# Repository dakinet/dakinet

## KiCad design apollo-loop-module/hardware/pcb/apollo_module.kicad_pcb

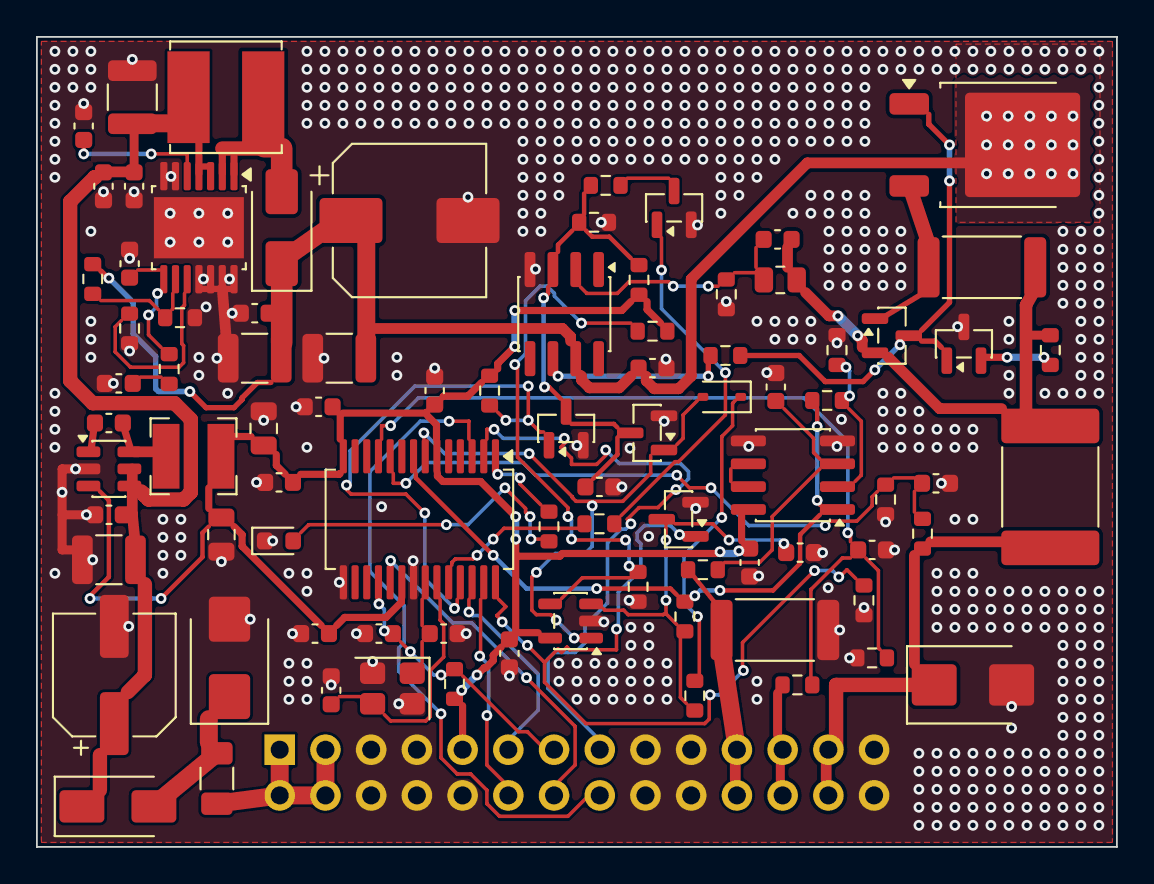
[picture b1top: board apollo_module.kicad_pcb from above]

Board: 2 copper layers, 60.0 x 45.0 mm, 86 parts (1 on the bottom side), 49 nets.

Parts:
C1: 47u/50V; CP_Elec_6.3x7.7
C2, C3, C4, C11: 10u/50V; C_1210_3225Metric
C5: 100u/50V; CP_Elec_8x10
C6, C10, C20, C23, C25, C28, C29: 100n; C_0603_1608Metric
C7, C16: 100p; C_0603_1608Metric
C8: 47n; C_0603_1608Metric
C9: 1u/50V; C_0603_1608Metric
C12: 22u/10V; C_0805_2012Metric
C13: 10u; C_0805_2012Metric
C14, C30: 10n; C_0603_1608Metric
C15, C35, C36, C37: 100n/50V; C_0603_1608Metric
C17, C18, C19, C24: 1n; C_0603_1608Metric
C26, C27: 27p; C_0603_1608Metric
C32: 1u; C_0603_1608Metric
D1: SS34; D_SMA
D2: SS210; D_SMA
D3: SMBJ36A; D_SMB
D4: BAT54J; D_SOD-323
D5: LED; LED_0603_1608Metric
D6: SMBJ28A; D_SMB
F1: 3A; Fuse_1206_3216Metric
F2: PTC 750mA/60V; Fuse_2920_7451Metric
J1: MATICNA 2x14; PinHeader_2x14_P2.54mm_Vertical
L1: 33uH SRN6045TA-330M; L_Bourns_SRN6045TA
L2: 15uH SRN4018-150M; L_Bourns-SRN4018
Q1: MJD122; TO-252-2
Q2, Q3, Q6, Q7: 2N7002; SOT-23
Q4: MMBT3904; SOT-23
Q5: MMBT5401; SOT-23
R1: 270k; R_0603_1608Metric
R2, R12, R16, R18, R21, R25, R26, R29: 10k; R_0603_1608Metric
R3: 82k; R_0603_1608Metric
R4: 2k2; R_0603_1608Metric
R5, R20, R27, R35: 1k; R_0603_1608Metric
R6: 15k; R_0603_1608Metric
R7: 3k24; R_0603_1608Metric
R8: 100; R_0603_1608Metric
R9, R15, R17, R28: 100k; R_0603_1608Metric
R10: 470; R_0603_1608Metric
R11: 91k; R_0805_2012Metric
R13: 2R0 1W; R_2512_6332Metric
R14: 10; R_0603_1608Metric
R19: 1R 1W; R_2512_6332Metric
R22: 40k2; R_0603_1608Metric
R24: 13k; R_0603_1608Metric
U1: TPS55340PWPR; Texas_HTSSOP-14-1EP_4.4x5mm_P0.65mm_EP3.4x5mm_Mask3.155x3.2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
U2: TPS560430X3FDBVR; SOT-23-6
U3: OPA197; SOIC-8_3.9x4.9mm_P1.27mm
U4: MCP6002; SOIC-8_3.9x4.9mm_P1.27mm
U6: MCP6561T-E/OT; SOT-23-5
U7: AVR64DD28-I/SS; SSOP-28_5.3x10.2mm_P0.65mm
Y1: 16MHz X322516MLB4SI; Crystal_SMD_3225-4Pin_3.2x2.5mm

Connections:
+3V3: C12.1, C13.1, C20.1, C23.1, C25.1, C28.1, C29.1, C32.1, J1.9, L2.2, R5.1, R9.2, R24.1, R29.2, U2.3, U4.8, U6.5, U7.6, U7.14, U7.20
+24V_IN: F1.1, J1.1, J1.2, J1.3, J1.4
+34V: C3.1, C4.1, C5.1, C15.1, C36.1, D2.1, Q1.2, R1.1, U3.7
BFB: R1.2, R2.1, U1.9
CB: C10.1, U2.1
CC: C6.1, R4.2
COMP: C7.1, R4.1, U1.8
DBG_RX: J1.16, U7.3
DBG_TX: J1.15, U7.2
EN_N: Q3.1, R9.1, U7.25
FB: C16.2, R11.2, R12.1, U3.2
FREQ: R3.1, U1.10
GND: C1.2, C2.2, C3.2, C4.2, C5.2, C6.2, C7.2, C8.2, C9.2, C11.2, C12.2, C13.2, C14.2, C15.2, C17.2, C18.2, C19.2, C20.2, C23.2, C24.2, C25.2, C26.2, C27.2, C28.2, C29.2, C30.2, C32.2, C35.2, C36.2, C37.2, D3.2, D5.1, D6.2, J1.5, J1.6, J1.7, J1.8, J1.10, J1.17, J1.18, J1.19, J1.20, J1.27, J1.28, Q2.2, Q3.2, Q5.3, Q6.2, Q7.2, R2.2, R3.2, R6.2, R12.2, R16.2, R18.2, R19.2, R21.2, R25.2, R28.2, U1.6, U1.7, U1.11, U1.12, U1.13, U1.14, U1.15, U2.2, U3.4, U4.4, U4.5, U6.2, U7.15, U7.21, Y1.2, Y1.4
IAMP: R22.2, R26.1, U4.1, U7.8
ISENSE: J1.21, J1.22, R19.1, R20.1
LED: R35.1, U7.1
LED_A: D5.2, R35.2
LOOP_DRV: C16.1, F2.1, Q4.2, R11.1, R13.2, R14.2
LOOP_IN: J1.23, J1.24, R17.1
LOOP_OUT: D3.1, F2.2, J1.25, J1.26, R15.1
NA: C19.1, R20.2, U4.3
NB: Q1.1, Q4.3, Q5.1, R10.2
NE: Q1.3, Q4.1, R13.1
NIVO: R8.1, U7.24
NIVO_G: Q2.1, R8.2
NM: R21.1, R22.1, U4.2
OCP: D4.2, Q6.1, U6.1, U7.7
OC_FB: D4.1, R27.1
OC_IN: C24.1, Q7.3, R26.2, R27.2, U6.3
OC_REF: R24.2, R25.1, U6.4
OC_RST: Q7.1, R28.1, U7.28
PE: Q5.2, R14.1
Q2D: Q2.3, R7.2
RESET: C30.1, J1.13, R29.1, U7.18
RX: J1.12, U7.27
SS: C8.1, U1.5
SW: D2.2, L1.2, U1.1, U1.2
SW3: C10.2, L2.1, U2.6
TX: J1.11, U7.26
U3OUT: R10.1, U3.6
U4B: U4.6, U4.7
UPDI: J1.14, U7.19
VIN: C1.1, C2.1, C9.1, C11.1, C35.1, C37.1, D1.1, L1.1, U1.3, U1.4, U2.4, U2.5
VIN_F: D1.2, D6.1, F1.2
VLOOP: C17.1, R15.2, R16.1, U7.10
VRET: C18.1, R17.2, R18.1, U7.11
VSET: C14.1, Q3.3, Q6.3, R5.2, R6.1, R7.1, U3.3
XIN: C26.1, U7.22, Y1.1
XO: C27.1, U7.23, Y1.3

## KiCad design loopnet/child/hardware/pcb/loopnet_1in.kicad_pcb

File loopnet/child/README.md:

# LoopNet 1IN v0.1 – uređaj sa jednim ulazom

Uređaj na LoopNet petlji (`../PROTOCOL.md` v0.2): napaja se sa dvožične linije, čita jedan kontakt sa EOL otpornicima,
odgovara strujnim impulsom 10 mA. Pločica 30 × 20 mm, 2 sloja, sve SMD na gornjoj strani (osim stezaljki).
**Nije protivpožarni uređaj.**

```
hardware/schematic/   kompletna.svg/png: cela šema na jednom listu, svi elementi povezani; skripta kompletna.py (schemdraw)
hardware/3d/          index.html + loopnet_1in.wrl: interaktivni 3D prikaz (three.js); pravi ga pcb/export_3d.py
hardware/pcb/         make_pcb.py (raspored + mreže) -> Freerouting -> finish_pcb.py -> DRC (build.sh)
                      jlc.py: Gerber zip, BOM_JLC.csv, CPL_JLC.csv; render.py: pcb_pregled.png
firmware/             C za ATtiny1616 (avr-gcc): ln_proto.c (dekoder okvira), crt0.S, test/test_decode.py
```

## Blokovi

| Blok | Delovi | Funkcija |
|---|---|---|
| Linija | J1 ulaz, J2 izlaz (prolazno, LA/LB), D1+D2 2× BAV99 most, D3 SMAJ40A | polaritet nebitan; TVS iza mosta |
| Izvor struje | Q1 MMBT5551, Q2 MMBT3904, R1 1M, R2 3k3, D4 BZT52C10, C1 10 µF | **konstantna** struja sa linije I = Vbe(Q2)/R2 + VP/R1 ≈ 167 + 24 µA; višak kroz Zener 10 V |
| 3,3 V | U1 HT7533-1 (SOT-89, JLC Basic), C2 10 µF, C3 100 nF | Iq 2,5 µA, ulaz do 24–30 V (VC je 10 V iza Zenera) |
| Prijem | R3, R4 4M7 sa **obe žice pre mosta** → LINE (PA7), R5 330k | čvor prati liniju i na silaznoj ivici (iza mosta bi TVS kapacitet držao vrh) |
| Prag | C4 10 nF na PA6 (AC0−), puni ga DAC0 ~50 µs svakih 10 ms | osnovni nivo (ADC na PA7) + 3,5 V |
| Odgovor | Q3 MMBT5551, R6 270 Ω, R7 1k, R8 100k | (3,3 − 0,75) V / 270 Ω ≈ 9,4 mA iz VP, samo za vreme odgovora (≤ 100 µs, ~0,27 W u impulsu) |
| Ulaz | J3, R9 2k2 sa PA3 (uključen ~50 µs), R10 1k + C5 1 nF → PA4 (ADC) | EOL 2k2 serijski + 2k2 paralelno kontaktu |
| Buđenje | PA5 (AC0 OUT) vodom na PA2 | AC0 u STANDBY-u ne postavlja zastavicu ni prekid (samo OUT pin i događaj); PA2 ima potpuno asinhronu detekciju ivice i budi CPU |
| Ostalo | D5 crvena LED + R11 1k (PB1), SW1 taster (PB2, interni pull-up), J4 UPDI 1,27 mm (VDD, PA0, GND) | |

## Odstupanja od zadatih delova (i zašto)

| Zadato | Urađeno | Razlog |
|---|---|---|
| MB6S | 2× BAV99 (SOT-23, 100 V, LCSC C2500 basic) | KiCad 7 nema MBS/TO-269AA otisak, a Vishay/Diodes datasheet-ovi nisu dostupni iz kontejnera – raspored pinova i otisak MB6S nisam mogao da proverim. BAV99 ima standardan raspored (1 A, 2 K, 3 sredina), 1,5 pF umesto ~15 pF. Struja ≤ 10 mA, napon ≤ 64 V (TVS). |
| BSS126 (~0,5 mA limiter) | izvor struje sa 2 NPN, ~180 µA | Limiter od 0,5 mA bez Zenera puni kondenzator do vrha (31 V) samo za vreme impulsa: osnovna struja u prozorima bi skakala do 60 mA za 120 uređaja i prag mastera bi bio pogrešan (PROTOCOL §0). Uz Zener uređaj vuče stalno I_CC; BSS126 ima V_GS(off) rasipanje ~2:1, pa bi I_CC bio 2:1 – Vbe/R izvor drži ±10 % (0–50 °C). |
| Referenca = „filtrirani osnovni nivo + 3 V“ (RC) | ADC meri osnovni nivo, DAC0 puni C4 (sample-hold) na +3,5 V | RC usrednjavanje zavisi od gustine impulsa; proračun u PROTOCOL §1.2 pokazuje da fiksni odnos ne radi za 15–26 V. VREF + DAC stalno uključeni ne bi stali u budžet. |

### Zamena Extended → Basic (JLC)

| Ranije (Extended) | Sada | Napomena |
|---|---|---|
| TPS7B8133DRV (WSON-6) | HT7533-1 SOT-89, C14289 | VC je ograničen Zenerom na 10 V, pa 40 V ulaz nije potreban; raspored pinova proveriti |
| BCX56-16 (SOT-89) | MMBT5551 SOT-23, C2145 | 160 V, 600 mA; ~0,27 W samo u impulsima odgovora |
| R6 240 Ω 0402 | 270 Ω 0603, C22966 | odgovor ~9,4 mA (spec 10 mA ±20 %) |
| R1 2M2 | 1M 0603, C22935 | +13 µA u izvoru struje |
| R5 330k 0402 | 330k 0603, C23137 | |
| R2, C4, C5 (bez broja) | C25890, C15195, C1523 | |
| zelena LED Everlight | KT-0603R crvena, C2286 | |

Ostaju Extended: ATtiny1616, SMAJ40A, BZT52C10, R3/R4 4M7 (Basic ide do 1 MΩ, a 1 MΩ bi trošio +25 µA), stezaljke KF350 – **5 vrsta umesto ~13**.
Basic status je iz javne liste JLC Basic delova (GitHub cpldcpu/TouchSynth, `parts/jlcpcb_basic_parts.csv`), ne direktno sa jlcpcb.com.

## Provera pinova (pre rutiranja)

| Deo | Raspored korišćen u `make_pcb.py` | Izvor |
|---|---|---|
| ATtiny1616-MNR (VQFN-20) | 1 PA2 (← AC_OUT), 2 PA3, 3 GND, 4 VDD, 5 PA4, 6 PA5, 7 PA6, 8 PA7, 9 PB5, 10 PB4, 11 PB3, 12 PB2, 13 PB1, 14 PB0, 15–18 PC0–PC3, 19 PA0/UPDI, 20 PA1, EP → GND | Microchip DS40001997C, tabela 5-1 i §4.2 (PDF pročitan), unakrsno sa ATtiny1616.atdf. AC0: PA7 = AINP0, PA6 = AINN0 (i DAC0 OUT), PA5 = AC0 OUT; ADC0: PA4 = AIN4, PA7 = AIN7 |
| HT7533-1 (SOT-89) | 1 GND, 2 VIN (+ tab), 3 VOUT | **NIJE provereno u datasheet-u** (holtek.com nedostupan); raspored iz Holtek HT75xx-1 opisa u pretrazi. Klonovi (npr. HX HT7533-1(H)) imaju 2 i 3 zamenjene – naručiti tačno C14289 (Holtek) i proveriti |
| BAV99 (SOT-23) | 1 anoda D1, 2 katoda D2, 3 katoda D1/anoda D2 | standardni Nexperia raspored (datasheet nije otvoren – nexperia.com blokiran) |
| MMBT5551, MMBT3904 (SOT-23) | 1 B, 2 E, 3 C | standardni raspored; MMBT3904 već korišćen u masteru |
| (Q3 je sada MMBT5551, isti raspored kao Q1) | 1 B, 2 E, 3 C | |
| SMAJ40A (SMA), BZT52C10 (SOD-123) | pad 1 = katoda (KiCad konvencija) | katoda na VP odnosno VC |
| TS-1187A, stezaljke 3,5 mm | 1–1 i 2–2 spojeni u tasteru | isti taster kao u masteru (C318884) |

## Potrošnja (procena iz datasheet-a ATtiny1616, tabele 37-6, 37-7, 37-9, V_DD = 3 V)

| Stavka | Proračun | µA |
|---|---|---|
| AC0 u low-power režimu (stalno) | tabela 37-9 | 45 |
| STANDBY + RTC/PIT (OSCULP32K) | 0,7 + 1,2 | 2 |
| HT7533-1 I_Q | | 3 |
| Uzorak ulaza i linije svakih 10 ms | buđenje 10 µs + ~100 µs na 5 MHz (1,7 mA) + ADC (0,33 mA); pobuda EOL 1,5 mA × 50 µs | 22 + 8 |
| Okviri: SKEN svakih 250 ms | IDLE na 5 MHz (0,4 mA) od START-a do svog para: 2,85 ms + ~127 × 0,15 ms ≈ 22 ms → 9 %; + prekidi | 40 (adresa 126: 70) |
| **Ukupno unutra** | | **≈ 120 µA (najviše ~150)** |
| Izvor struje I_CC | 0,55 V / 3,3 kΩ + 24 V / 1 MΩ (25 °C); Vbe −2 mV/°C | 191 (174 pri 50 °C) |
| Delitelj prijema (sa linije, mimo izvora) | 31 V / 4,7 MΩ | 6 |
| **Struja sa linije** | konstantna, ne zavisi od rada MCU-a | **≈ 197 µA** |

Rezerva izvora prema unutrašnjoj potrošnji je ~10–40 µA (manja na toploti). Ako merenje pokaže manjak:
R2 = 3k0 (+17 µA) ili ređi SKEN (500 ms). **Ništa od ovoga nije izmereno** – sve su tipične vrednosti iz datasheet-a.

## Pločica

- 30 × 20 mm, 2 sloja, 1,6 mm; GND površine na oba sloja, šivene via; via u centralnim padovima U1 i U2 postavljene pre rutiranja.
- Razmaci: podrazumevano 0,15 mm / vod 0,2 mm; mreže sa linije (LA, LB, VP, QB, QE) **0,3 mm** (`loopnet_1in.kicad_dru`;
  IPC-2221 B4 za 31–100 V traži 0,13 mm, izmereno najmanje 0,30 mm), vodovi linije 0,4 mm. Bakar do ivice ≥ 0,3 mm.
- DRC (`pcbnew.WriteDRCReport`): **0 grešaka, 0 nepovezanih padova**; ostaje 31 informativna napomena
  „library '' not in configuration“ (otisci učitani skriptom, isto kao kod mastera).
- R3/R4 (delitelj prijema) stoje uz MCU: visokoimpedantni vod LINE je 6,6 mm (ranije 32,4 mm); LED je premeštena levo.
- Oznake komponenti su na F.Fab (na silk sloju nema mesta); natpisi na donjoj strani.
- Tok: `cd hardware/pcb && ./build.sh && python3.12 jlc.py` (Freerouting 1.9.0 u `/tmp/claude-0/fr/fr.jar` ili `FREEROUTING_JAR`).

### Narudžbina kod JLCPCB

`loopnet_1in_gerber.zip`, `BOM_JLC.csv`, `CPL_JLC.csv`. Kolona „Provera“ u BOM-u: S = LCSC broj viđen u rezultatima pretrage
(LCSC/JLC stranica), M = deo već u BOM-u mastera, **? = nije potvrđeno** (samo R3/R4 4M7 – C23163 viđen samo u pretrazi). J4 (UPDI) se ne montira.
Rotacije u CPL su KiCad-ove – proveri u JLC pregledu (SOT-23, SOT-89, WSON, VQFN). Stezaljke Kefa KF350-3.5-2P: uporedi
crtež sa otiskom Phoenix PT 1,5/2-3,5-H (raspon 3,5 mm, rupa 1,2 mm).

## Poznata ograničenja v0.1

- Nema zaštite ulaza J3 od prenapona osim R10 1k i diodi pina; kabl ulaza treba da bude kratak / u istom kućištu.
- UPDI programiranje: ili linija priključena, ili 3,3 V na J4-1 (struja unazad kroz HT7533 nije proverena).

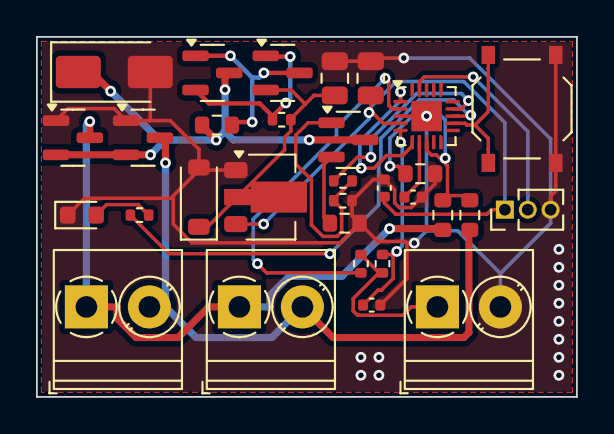
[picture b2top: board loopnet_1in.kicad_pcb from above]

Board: 2 copper layers, 30.0 x 20.0 mm, 31 parts (0 on the bottom side), 21 nets.

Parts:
C1, C2: 10u/25V; C_0805_2012Metric
C3: 100n; C_0402_1005Metric
C4: 10n; C_0402_1005Metric
C5: 1n; C_0402_1005Metric
D1, D2: BAV99; SOT-23
D3: SMAJ40A; D_SMA
D4: BZT52C10; D_SOD-123
D5: LED; LED_0603_1608Metric
J1: LINIJA ULAZ; TerminalBlock_Phoenix_PT-1,5-2-3.5-H_1x02_P3.50mm_Horizontal
J2: LINIJA IZLAZ; TerminalBlock_Phoenix_PT-1,5-2-3.5-H_1x02_P3.50mm_Horizontal
J3: ULAZ; TerminalBlock_Phoenix_PT-1,5-2-3.5-H_1x02_P3.50mm_Horizontal
J4: UPDI; PinHeader_1x03_P1.27mm_Vertical
Q1, Q3: MMBT5551; SOT-23
Q2: MMBT3904; SOT-23
R1: 1M; R_0603_1608Metric
R2: 3k3; R_0402_1005Metric
R3, R4: 4M7; R_0603_1608Metric
R5: 330k; R_0603_1608Metric
R6: 270; R_0603_1608Metric
R7, R10, R11: 1k; R_0402_1005Metric
R8: 100k; R_0402_1005Metric
R9: 2k2; R_0402_1005Metric
SW1: TASTER; SW_Push_1P1T_XKB_TS-1187A
U1: HT7533-1; SOT-89-3
U2: ATtiny1616-MNR; VQFN-20-1EP_3x3mm_P0.4mm_EP1.7x1.7mm

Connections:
AC_OUT: U2.1, U2.6
BTN: SW1.1, U2.12
GND: C1.2, C2.2, C3.2, C4.2, C5.2, D1.1, D2.1, D3.2, D4.2, D5.1, J3.2, J4.3, R5.2, R6.2, R8.2, SW1.2, U1.1, U2.3, U2.21
INP: J3.1, R9.2, R10.1
IN_DRV: R9.1, U2.2
IN_SENSE: C5.1, R10.2, U2.5
LA: D1.3, J1.1, J2.1, R3.1
LB: D2.3, J1.2, J2.2, R4.1
LED: R11.1, U2.13
LED_A: D5.2, R11.2
LINE: R3.2, R4.2, R5.1, U2.8
QB: Q1.1, Q2.3, R1.2
QE: Q1.2, Q2.1, R2.1
QSB: Q3.1, R7.2, R8.1
QSE: Q3.2, R6.1
SINK: R7.1, U2.14
UPDI: J4.2, U2.19
VC: C1.1, D4.1, Q2.2, R2.2, U1.2
VDD: C2.1, C3.1, J4.1, U1.3, U2.4
VP: D1.2, D2.2, D3.1, Q1.3, Q3.3, R1.1
VTHR: C4.1, U2.7

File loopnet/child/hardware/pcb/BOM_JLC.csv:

Comment,Designator,Footprint,LCSC Part #,Manufacturer Part,Provera,Note
10u/25V,"C1,C2",C_0805_2012Metric,C15850,Samsung CL21A106KAYNNNE,M,B; X5R 25 V
100n,C3,C_0402_1005Metric,C1525,Samsung CL05B104KO5NNNC,S,B
10n,C4,C_0402_1005Metric,C15195,Samsung CL05B103KB5NNNC,S,B
1n,C5,C_0402_1005Metric,C1523,FH 0402B102K500NT,S,B
BAV99,"D1,D2",SOT-23,C2500,"Nexperia BAV99,215",S,B
SMAJ40A,D3,D_SMA,C3719895,Taiwan Semi SMAJ40A,S,E; nema Basic TVS 40 V
BZT52C10,D4,D_SOD-123,C2103,JSCJ BZT52C10,S,E; nema Basic zener
LED,D5,LED_0603_1608Metric,C2286,Hubei KENTO KT-0603R,S,B; crvena
LINIJA ULAZ,J1,"TerminalBlock_Phoenix_PT-1,5-2-3.5-H_1x02_P3.50mm_Horizontal",C474892,Kefa KF350-3.5-2P,S,"E; THT 3,5 mm; uporedi crtež sa Phoenix PT 1,5/2-3,5-H"
LINIJA IZLAZ,J2,"TerminalBlock_Phoenix_PT-1,5-2-3.5-H_1x02_P3.50mm_Horizontal",C474892,Kefa KF350-3.5-2P,S,"E; THT 3,5 mm; uporedi crtež sa Phoenix PT 1,5/2-3,5-H"
ULAZ,J3,"TerminalBlock_Phoenix_PT-1,5-2-3.5-H_1x02_P3.50mm_Horizontal",C474892,Kefa KF350-3.5-2P,S,"E; THT 3,5 mm; uporedi crtež sa Phoenix PT 1,5/2-3,5-H"
UPDI,J4,PinHeader_1x03_P1.27mm_Vertical,,,,"UPDI: rupe 1,27 mm, ne montira se (pogo ili zalemljene žice)"
MMBT5551,"Q1,Q3",SOT-23,C2145,JSCJ MMBT5551,S,B; 160 V
MMBT3904,Q2,SOT-23,C20526,CJ MMBT3904,M,B
1M,R1,R_0603_1608Metric,C22935,UNI-ROYAL 0603WAF1004T5E,S,B
3k3,R2,R_0402_1005Metric,C25890,UNI-ROYAL 0402WGF3301TCE,S,B; odredjuje I_CC
4M7,"R3,R4",R_0603_1608Metric,C23163,UNI-ROYAL 0603WAF4704T5E,?,E; nema Basic >1 MOhm (1M bi trosio +25 µA)
330k,R5,R_0603_1608Metric,C23137,UNI-ROYAL 0603WAF3303T5E,S,B
270,R6,R_0603_1608Metric,C22966,UNI-ROYAL 0603WAF2700T5E,S,"B; odredjuje ~9,4 mA odgovora"
1k,"R7,R10,R11",R_0402_1005Metric,C11702,UNI-ROYAL 0402WGF1001TCE,S,B
100k,R8,R_0402_1005Metric,C25741,UNI-ROYAL 0402WGF1003TCE,S,B
2k2,R9,R_0402_1005Metric,C25879,UNI-ROYAL 0402WGF2201TCE,S,B
TASTER,SW1,SW_Push_1P1T_XKB_TS-1187A,C318884,XKB TS-1187A-B-A-B,M,B
HT7533-1,U1,SOT-89-3,C14289,Holtek HT7533-1,S,"B; 1 GND, 2 VIN, 3 VOUT - PROVERI datasheet (klonovi imaju drugi raspored)"
ATtiny1616-MNR,U2,VQFN-20-1EP_3x3mm_P0.4mm_EP1.7x1.7mm,C507118,Microchip ATTINY1616-MNR,S,E; nema Basic zamene

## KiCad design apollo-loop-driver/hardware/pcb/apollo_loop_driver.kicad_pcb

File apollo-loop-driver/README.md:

# Apollo XP95 laboratorijski drajver petlje

Elektronika koja sama napaja Apollo adresabilnu petlju, proziva uređaje XP95/Discovery protokolom
i čita njihove strujne odgovore. **Samo za laboratoriju** – uređaj nije sertifikovan po EN 54 i ne sme
se priključiti na petlju koja štiti ljude ili objekat.

| | |
|---|---|
| Napajanje | 24 V DC (21–28 V), kao protivpožarna centrala |
| Petlja | 24,2 V osnovni nivo, 31,2 V impuls, do ≈ 540 mA (ograničenje), PTC 750 mA |
| Mozak | RP2040 na ploči (flash W25Q16, kristal 12 MHz), MicroPython, PIO + DMA |
| USB | USB-B, galvanski odvojen preko ADuM3160 (posebna masa GND_USB) |
| Pločica | 130 × 95 mm, 2 sloja, sve na ploči (bez modula), 9 funkcionalnih blokova |

## Sadržaj

```
hardware/schematic/   električna šema u 4 lista (SVG/PNG) i skripte koje je crtaju (schemdraw)
hardware/pcb/         KiCad 7 pločica, Gerber + drill (apollo_loop_driver_gerber.zip), BOM, DRC izveštaj
  make_pcb.py         raspored komponenti i mreže (izvor istine za pločicu)
  finish_pcb.py       uvoz vodova iz Freerouting-a, GND površine i šivenje
  build.sh            ceo tok: raspored -> rutiranje -> DRC
firmware/             MicroPython za Pico: config.py, loopdrv.py, main.py
```

## Pločica (v0.2)
Sve je na ploči, bez spoljnih modula. Blokovi (okviri i nazivi na F.Fab sloju):

| Blok | Sadržaj | Pravila rasporeda |
|---|---|---|
| 1 USB izolacija | USB-B, ADuM3160, 27 Ω | posebna masa GND_USB, traka 2,3 mm bez bakra ispod U8 |
| 2 Ulaz 24 V | stezaljka, osigurač 3 A, SS34 | na ivici, kratki vodovi |
| 3 Boost 34 V | LM2587S-ADJ, 100 µH, SS56, 2×470 µF + 10 µF + 1 µF | po TI referenci „24-V To 36-V Boost“ (slika 20) i rasporedu sa slike 63: C31 4,2 mm od VIN, L1 4,7 mm od SW, C5/C63 4–5 mm od katode, FB/COMP otpornici 6–8 mm od pinova, 16 termalnih via ispod tab-a |
| 4 Napajanje 5V/3V3 | R-78E5.0, AP2112K-3.3 | ulazni/izlazni kondenzatori uz pinove |
| 5 MCU | RP2040, W25Q16, 12 MHz, BOOTSEL/RESET, SWD | 100 nF uz svaki IOVDD, kristal uz XIN/XOUT, 9 via u centralnom padu |
| 6 Referenca i nivo | REF3033, delitelj, 2N7002 | daleko od SW čvora |
| 7 Drajver 34 V | OPA197, TIP122 položen na hladnjak Aavid TV5G, BC847, 1,2 Ω | V+ OPA197 okrenut ka C13/C58 |
| 8 Izlaz i zaštita | PTC 750 mA, SMBJ36A, delitelj VLOOP + 1 nF | |
| 9 Merenje struje | šant 1 Ω, MCP6002 (×5,02), MCP6561, VRET + 1 nF | odvojeno od boost-a |
| 10 Zaštita KS | MCP6561 + zadrška (D6/R36), Q6 gasi VSET, Q7 briše | prag ≈ 494 mA, reakcija u µs |

Razmaci: signali 0,15 mm / 0,2 mm vod; mreže do 34 V **0,6 mm** (IPC-2221 B2, spoljni sloj);
USB strana prema ostatku **2 mm** (`apollo_loop_driver.kicad_dru`). GND površine na oba sloja,
šivene via na 5 mm.

Razdvajanje i filtri: 100 nF uz svaki IC (RP2040 ×8, flash, ADuM ×2, op-pojačavači, REF3033),
1 µF na VREG/DVDD, ADuM VBUS/VDD 1–10 µF; boost 1 µF + 100 µF ulaz, 1 µF + 2×220 µF izlaz;
RC filteri na ADC ulazima (VLOOP, VRET 1 nF, IAMP 1 kΩ/1 nF), PWM prag 10 kΩ/1 µF.

**Pre naručivanja proveri** raspored pinova iz datasheet-a: LM2587 (TO-263-5: 1 COMP, 2 FB, 3 GND/tab, 4 SW, 5 VIN),
ADuM3160 (SOIC-16W), RP2040 (QFN-56), W25Q16JV (SOIC-8 208 mil), AP2112K (SOT-23-5), REF3033, MCP6561,
2N7002/BC847 i TIP122. Pločica je napravljena programski (`make_pcb.py`), bez KiCad šeme (.kicad_sch).

## Narudžbina kod JLCPCB
`python3.12 hardware/pcb/jlc.py` (posle `build.sh`) pravi:
- `apollo_loop_driver_gerber.zip` – Gerber + drill za izradu pločice (2 sloja, 1,6 mm)
- `BOM_JLC.csv` – sve stavke sa LCSC brojevima (kolone Comment, Designator, Footprint, LCSC Part #)
- `CPL_JLC.csv` – pozicije delova (Designator, Mid X, Mid Y, Layer, Rotation)

Zamene zbog JLC kataloga: L1 SRR1280-101M (isti otisak kao SRR1260, Isat 2,0 A, vršna struja ≈ 1,4 A),
Q4 MMBT3904 umesto BC847, tasteri XKB TS-1187A, kondenzatori kristala 33 pF (kristal C9002, CL 20 pF).
Hladnjak TV5G nije u katalogu – montira se ručno. Montažne rupe H1–H5 (sva četiri ugla i sredina donje ivice): Ø3,2 mm za M3, pometalisane sa prstenom 6,4 mm na obe strane, nisu povezane na masu (kućište ne sme da napravi zemljospoj kad je pločica na petlji centrale). Rotacije u CPL su KiCad-ove: proveri ih u JLC pregledu
pre potvrde (najčešće treba okrenuti SOT-23, SOIC i QFN). USB-B10-BRW: pre narudžbine uporedi crtež
otiska sa OST USB-B1HSxx. Malo na stanju: ADuM3160 i LM2587S-ADJ.

## Kratak spoj i prekid petlje
- **Kratak spoj / preopterećenje:** šant R14 (1 Ω) meri struju petlje; kad pređe ≈ 500 mA, U12 okida za nekoliko µs,
  Q6 spušta VSET i petlja se gasi bez učešća procesora. D6/R36 drže stanje (latch) dok firmver ne pusti OC_RST.
  Do okidanja struju ograničava Q4/R7 na ≈ 540 mA. Firmver javlja `kratak_spoj` i petlja se pali ponovo komandom `on`.
- **Prekid linije (otvoreno kolo):** napon na povratku petlje (J3, VRET) < 50 % izlaza → `prekid_petlje`.
- Posle uključenja zaštita je blokirana 20 ms (punjenje kapaciteta petlje, do 0,5 µF).

## Snaga delova
| Deo | Normalno (0,5 A) | Kratak spoj (≤ 0,54 A do okidanja) | Izabrano |
|---|---|---|---|
| R7 1,2 Ω | 0,30 W | 0,35 W | 2512, 1 W (pulsni, npr. Vishay WSL2512 / Yageo PE2512) |
| R14 1 Ω | 0,25 W | 0,29 W | 2512, 1 W, 1 % |
| TIP122 | (34 − 24 V) × I = 5 W pri 500 mA, 0,5 W pri 50 mA | kratko, do okidanja | TO-220 položen + TV5G |

**Hladnjak:** Aavid TV5G ima ≈ 21 °C/W. Uz TIP122 (θjc 1,92 °C/W) i 40 °C okoline, TV5G je dovoljan do ≈ 200 mA
trajno (Tj ≈ 90 °C). Za trajnih 500 mA treba hladnjak ≤ 8 °C/W ili ventilator (Tj bi sa TV5G bila ≈ 157 °C).
Tab TIP122 je kolektor (+34 V) – hladnjak ne sme dodirivati masu, ili koristi izolacionu podlošku.

## Firmver
Prvo uključenje: drži BOOTSEL, priključi USB i prevuci MicroPython UF2 za RP2040 (Raspberry Pi Pico build radi, isti pinovi). Zatim kopiraj `firmware/*.py` (npr. Thonny). Na USB serijskom portu:

```
on | off | status
poll 5            prozove adresu 5
scan 1 126        traži sve uređaje
sniff 300         sluša pravu centralu 300 ms (drajver ugašen)
set T_JEDAN 650   menja vreme u RAM-u
get               ispiše vremena okvira
```

Vremena okvira u `config.py` su preuzeta iz dokumenta o Linux drajveru za Apollo petlju
(`docs/apollo_protokol_izvor.md`): INIT 1650 µs, bit 0 = 200 + 300 µs, bit 1 = 850 + 300 µs, prijemni bit 1700 µs,
prozor odgovora 350–600 µs. **Nisu izmerena**: polaritet (HIGH = 31 V?), redosled bitova i polja odgovora treba
potvrditi na pravoj centrali u režimu **sniff**:

- centrala L+ → J3-1 (LOOP IN +) i dalje ka uređajima
- centrala L− → GND pločice (J1-2), ploča napajana sa 24 V na J1
- L− uređaja → J3-2 (ide kroz šant R14)
- **J2 (LOOP OUT) ostaje nepovezan**, drajver ugašen (`off`)

## Soteria / CoreProtocol
Soteria javljači su kompatibilni unazad: na XP95/Discovery petlji rade kao Discovery uređaji
(analogna vrednost, tip, adresa, LED). Ova pločica ih zato podržava u tom režimu.
Funkcije samo za CoreProtocol (soft adresiranje, serijski broj, checksum, adrese do 254, režim 35 V)
traže nepoznatu specifikaciju i izlazni stepen do ≈ 48 V – to je plan za v2.

## Izvori
- US8428153B2 – opis XP95 okvira (reset 1,5 ms, 10 bitova, 21 takt, 21-bitni strujni odgovor)
- Apollo Test Set PP2625, Loop Interface PP5099, XP95 I.S. PP1095

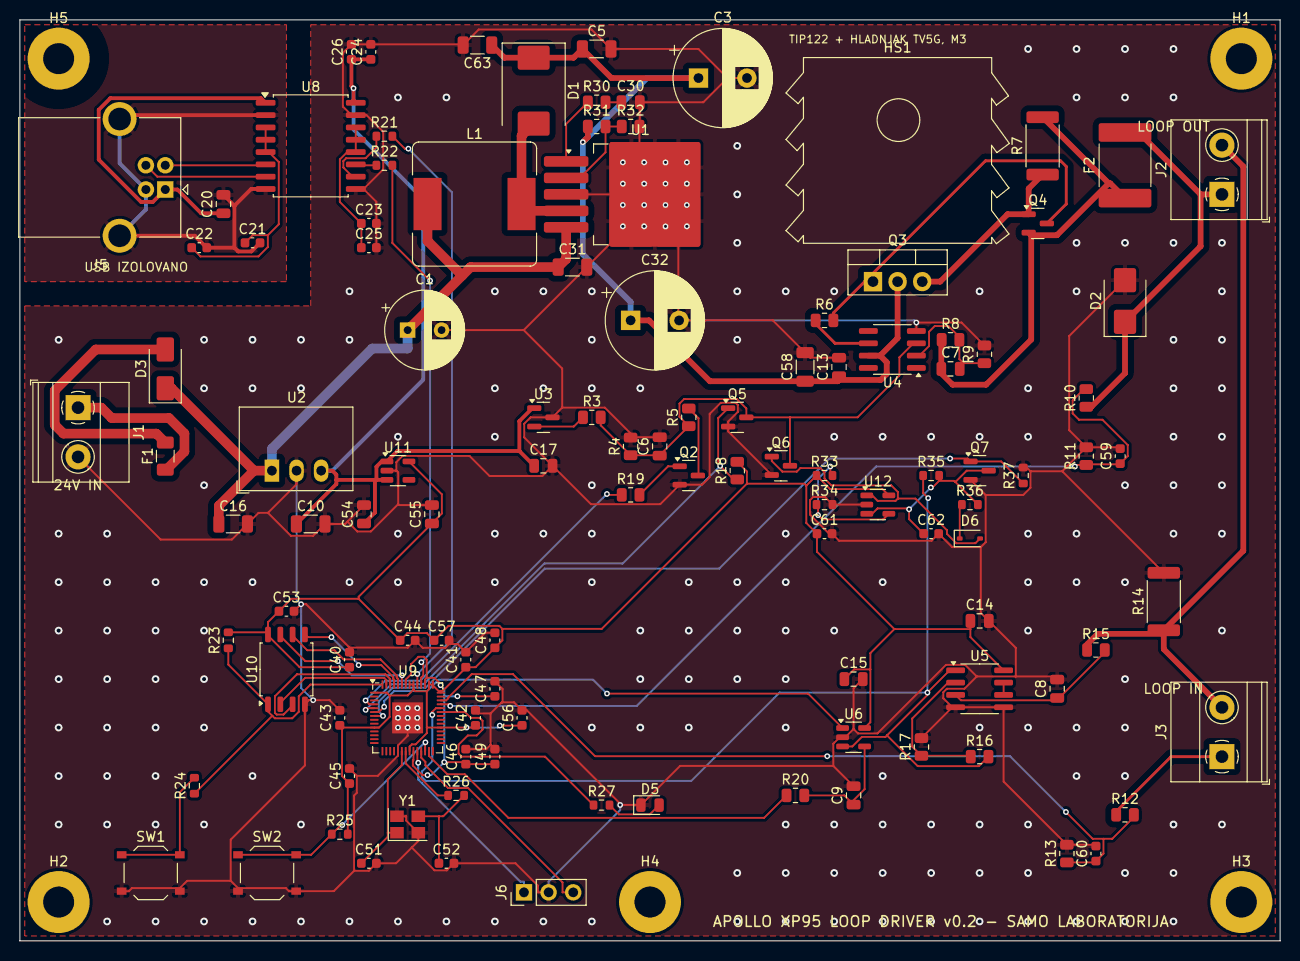
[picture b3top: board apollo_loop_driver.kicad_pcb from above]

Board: 2 copper layers, 130.0 x 95.0 mm, 118 parts (0 on the bottom side), 65 nets.

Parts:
C1: 100u/50V; CP_Radial_D8.0mm_P3.50mm
C3, C32: 470u/50V lowESR; CP_Radial_D10.0mm_P5.00mm
C5, C31, C58: 1u/50V; C_1206_3216Metric
C6: 10n; C_0805_2012Metric
C7: 100p; C_0805_2012Metric
C8: 1n; C_0805_2012Metric
C9, C54, C55: 1u; C_0805_2012Metric
C10: 10u; C_1206_3216Metric
C13, C14, C15, C17: 100n; C_0805_2012Metric
C16: 4u7/50V; C_1206_3216Metric
C20: 10u; C_0805_2012Metric
C21, C23, C26, C47, C48: 1u; C_0603_1608Metric
C22, C24, C25, C40, C41, C42, C43, C44, C45, C46, C49, C53, C56, C57, C61: 100n; C_0603_1608Metric
C30: 680n; C_0805_2012Metric
C51, C52: 33p; C_0603_1608Metric
C59, C60, C62: 1n; C_0603_1608Metric
C63: 10u/50V; C_1206_3216Metric
D1: SS56; D_SMC
D2: SMBJ36A; D_SMB
D3: SS34; D_SMA
D5: LED; LED_0805_2012Metric
D6: BAT54J; D_SOD-323
F1: 3A; Fuse_1206_3216Metric
F2: PTC 750mA/60V; Fuse_2920_7451Metric
H1, H2, H3, H4, H5: M3; MountingHole_3.2mm_M3_Pad
HS1: Aavid TV5G; Heatsink_AAVID_TV5G_TO220_Horizontal
J1: 24V IN; TerminalBlock_Phoenix_MKDS-1,5-2-5.08_1x02_P5.08mm_Horizont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
J2: LOOP OUT; TerminalBlock_Phoenix_MKDS-1,5-2-5.08_1x02_P5.08mm_Horizont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
J3: LOOP IN; TerminalBlock_Phoenix_MKDS-1,5-2-5.08_1x02_P5.08mm_Horizont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
J5: USB-B; USB_B_OST_USB-B1HSxx_Horizontal
J6: SWD; PinHeader_1x03_P2.54mm_Vertical
L1: 100uH SRR1280-101M; L_Bourns_SRR1260
Q2, Q5, Q6, Q7: 2N7002; SOT-23
Q3: TIP122 + hladnjak; TO-220-3_Vertical
Q4: MMBT3904; SOT-23
R3, R6, R15: 1k; R_0805_2012Metric
R4: 15k; R_0805_2012Metric
R5: 3k24; R_0805_2012Metric
R7: 1R2 1W; R_2512_6332Metric
R8: 91k; R_0805_2012Metric
R9, R11, R13, R17, R20: 10k; R_0805_2012Metric
R10, R12, R18: 100k; R_0805_2012Metric
R14: 1R 1W; R_2512_6332Metric
R16: 40k2; R_0805_2012Metric
R19: 100; R_0805_2012Metric
R21, R22: 27; R_0603_1608Metric
R23, R25, R34, R35: 10k; R_0603_1608Metric
R24, R26, R27, R36: 1k; R_0603_1608Metric
R30: 3k0; R_0805_2012Metric
R31: 53k6; R_0805_2012Metric
R32: 2k; R_0805_2012Metric
R33: 3k3; R_0603_1608Metric
R37: 100k; R_0603_1608Metric
SW1: BOOTSEL; SW_Push_1P1T_XKB_TS-1187A
SW2: RESET; SW_Push_1P1T_XKB_TS-1187A
U1: LM2587S-ADJ; TO-263-5_TabPin3
U2: R-78E5.0-0.5; Converter_DCDC_RECOM_R-78E-0.5_THT
U3: REF3033; SOT-23
U4: OPA197; SOIC-8_3.9x4.9mm_P1.27mm
U5: MCP6002; SOIC-8_3.9x4.9mm_P1.27mm
U6, U12: MCP6561; SOT-23-5
U8: ADuM3160; SOIC-16W_7.5x10.3mm_P1.27mm
U9: RP2040; QFN-56-1EP_7x7mm_P0.4mm_EP3.2x3.2mm
U10: W25Q16JVSS; SOIC-8_5.23x5.23mm_P1.27mm
U11: AP2112K-3.3; SOT-23-5
Y1: 12MHz; Crystal_SMD_3225-4Pin_3.2x2.5mm

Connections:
+3V3: C14.1, C15.1, C40.1, C41.1, C42.1, C43.1, C44.1, C45.1, C48.1, C53.1, C55.1, C56.1, C57.1, C61.1, R18.2, R23.2, R25.2, R33.1, U5.8, U6.5, U9.1, U9.10, U9.22, U9.33, U9.42, U9.43, U9.44, U9.48, U9.49, U10.8, U11.5, U12.5
+5V: C10.1, C17.1, C24.1, C26.1, C54.1, U2.3, U3.1, U8.16, U11.1, U11.3
+24V: C1.1, C16.1, C31.1, D3.1, L1.1, U1.5, U2.1
+24V_IN: F1.1, J1.1
+34V: C3.1, C5.1, C13.1, C32.1, C58.1, C63.1, D1.1, Q3.2, R31.1, U4.7
BFB: R31.2, R32.1, U1.2
BIT: U6.1, U9.6
BOOT: R24.2, SW1.1
CC: C30.1, R30.2
COMP: R30.1, U1.1
DM_ISO: R22.1, U8.11
DP_ISO: R21.1, U8.10
DVDD: C46.1, C47.1, C49.1, U9.23, U9.45, U9.50
EN_N: Q5.1, R18.1, U9.5
FB: C7.2, R8.2, R9.1, U4.2
GND: C1.2, C3.2, C5.2, C6.2, C8.2, C9.2, C10.2, C13.2, C14.2, C15.2, C16.2, C17.2, C23.2, C24.2, C25.2, C26.2, C30.2, C31.2, C32.2, C40.2, C41.2, C42.2, C43.2, C44.2, C45.2, C46.2, C47.2, C48.2, C49.2, C51.2, C52.2, C53.2, C54.2, C55.2, C56.2, C57.2, C58.2, C59.2, C60.2, C61.2, C62.2, C63.2, D2.2, D5.1, J1.2, J6.2, Q2.2, Q5.2, Q6.2, Q7.2, R4.2, R9.2, R11.2, R13.2, R14.2, R17.2, R32.2, R34.2, R37.2, SW1.2, SW2.2, U1.3, U2.2, U3.3, U4.4, U5.4, U5.5, U6.2, U8.9, U8.15, U9.19, U9.57, U10.4, U11.2, U12.2, Y1.2, Y1.4
GND_USB: C20.2, C21.2, C22.2, J5.4, J5.5, U8.2, U8.8
IAMP: R16.2, R35.1, U5.1, U6.3, U9.38
ISENSE: J2.2, J3.2, R14.1, R15.1
LED: R27.1, U9.37
LED_A: D5.2, R27.2
LOOP_DRV: C7.1, F2.1, Q4.2, R7.2, R8.1
LOOP_IN: J3.1, R12.1
LOOP_OUT: D2.1, F2.2, J2.1, R10.1
NA: C8.1, R15.2, U5.3
NB: Q3.1, Q4.3, R6.2
NE: Q3.3, Q4.1, R7.1
NIVO: R19.1, U9.4
NIVO_G: Q2.1, R19.2
NM: R16.1, R17.1, U5.2
OCP: D6.2, Q6.1, U12.1
OC_FB: D6.1, R36.1
OC_IN: C62.1, Q7.3, R35.2, R36.2, U12.3
OC_REF: R33.2, R34.1, U12.4
OC_RST: Q7.1, R37.1, U9.7
PRAG: R20.1, U9.27
PRAG_F: C9.1, R20.2, U6.4
Q2D: Q2.3, R5.2
QSCLK: U9.52, U10.6
QSD0: U9.53, U10.5
QSD1: U9.55, U10.2
QSD2: U9.54, U10.3
QSD3: U9.51, U10.7
QSS: R23.1, R24.1, U9.56, U10.1
REF: R3.1, U3.2
RUN: R25.1, SW2.1, U9.26
SW: D1.2, L1.2, U1.4
SWCLK: J6.1, U9.24
SWDIO: J6.3, U9.25
U4OUT: R6.1, U4.6
U5B: U5.6, U5.7
USB_DM: R22.2, U9.46
USB_DM_C: J5.2, U8.6
USB_DP: R21.2, U9.47
USB_DP_C: J5.3, U8.7
VBUS_USB: C20.1, J5.1, U8.1
VDD1: C21.1, C22.1, U8.3, U8.4, U8.5
VDD2: C23.1, C25.1, U8.12, U8.13, U8.14
VIN_F: D3.2, F1.2
VLOOP: C59.1, R10.2, R11.1, U9.39
VRET: C60.1, R12.2, R13.1, U9.40
VSET: C6.1, Q5.3, Q6.3, R3.2, R4.1, R5.1, U4.3
XIN: C51.1, U9.20, Y1.1
XO: C52.1, R26.2, Y1.3
XOUT: R26.1, U9.21

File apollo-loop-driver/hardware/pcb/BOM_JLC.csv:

Comment,Designator,Footprint,LCSC Part #,Manufacturer Part,Note
100u/50V,C1,CP_Radial_D8.0mm_P3.50mm,C88859,Rubycon 50YXJ100M,"THT; proveri D8/P3,5"
470u/50V lowESR,"C3,C32",CP_Radial_D10.0mm_P5.00mm,C2902875,Rubycon 50ZLJ470M,THT low-ESR; proveri D10/P5
1u/50V,"C5,C31,C58",C_1206_3216Metric,C1848,Samsung CL31B105KBHNNNE,
10n,C6,C_0805_2012Metric,C1710,Samsung CL21B103KBANNNC,
100p,C7,C_0805_2012Metric,C1790,Samsung CL21C101JBANNNC,C0G
1n,C8,C_0805_2012Metric,C46653,Samsung CL21B102KBCNNNC,
1u,"C9,C54,C55",C_0805_2012Metric,C28323,Samsung CL21B105KBFNNNE,
10u,C10,C_1206_3216Metric,C13585,Samsung CL31A106KBHNNNE,
100n,"C13,C14,C15,C17",C_0805_2012Metric,C49678,Yageo CC0805KRX7R9BB104,
4u7/50V,C16,C_1206_3216Metric,C29823,FH 1206B475K500NT,
10u,C20,C_0805_2012Metric,C15850,Samsung CL21A106KAYNNNE,
1u,"C21,C23,C26,C47,C48",C_0603_1608Metric,C15849,Samsung CL10A105KB8NNNC,
100n,"C22,C24,C25,C40,C41,C42,C43,C44,C45,C46,C49,C53,C56,C57,C61",C_0603_1608Metric,C14663,Yageo CC0603KRX7R9BB104,
680n,C30,C_0805_2012Metric,C282780,CCTC TCC0805X7R684K500DT,
33p,"C51,C52",C_0603_1608Metric,C1663,Samsung CL10C330JB8NNNC,C0G; kristal C9002 CL=20 pF
1n,"C59,C60,C62",C_0603_1608Metric,C1588,Samsung CL10B102KB8NNNC,
10u/50V,C63,C_1206_3216Metric,C13585,Samsung CL31A106KBHNNNE,X5R 50 V; X7R zamena C303950
SS56,D1,D_SMC,C698825,Yangjie SS56,SMC
SMBJ36A,D2,D_SMB,C353364,SMBJ36A,unidirekciona
SS34,D3,D_SMA,C8678,MDD SS34,
LED,D5,LED_0805_2012Metric,C2297,KENTO KT-0805G,zelena
BAT54J,D6,D_SOD-323,C130415,"Nexperia BAT54J,115",
3A,F1,Fuse_1206_3216Metric,C14165,Littelfuse 0466003.NRHF,"32 V, ulaz je 24 V"
PTC 750mA/60V,F2,Fuse_2920_7451Metric,C47513,Ruilon SMD2920P075TF/60,
Aavid TV5G,HS1,Heatsink_AAVID_TV5G_TO220_Horizontal,,,Aavid/Boyd TV5G nije u LCSC katalogu - montirati rucno (M3 zavrtanj kroz TIP122 i hladnjak)
24V IN,J1,"TerminalBlock_Phoenix_MKDS-1,5-2-5.08_1x02_P5.08mm_Horizontal",C5183929,"Phoenix MKDS 1,5/2-5,08",THT; zamena Kefa KF128-5.08-2P C474952
LOOP OUT,J2,"TerminalBlock_Phoenix_MKDS-1,5-2-5.08_1x02_P5.08mm_Horizontal",C5183929,"Phoenix MKDS 1,5/2-5,08",THT; zamena Kefa KF128-5.08-2P C474952
LOOP IN,J3,"TerminalBlock_Phoenix_MKDS-1,5-2-5.08_1x02_P5.08mm_Horizontal",C5183929,"Phoenix MKDS 1,5/2-5,08",THT; zamena Kefa KF128-5.08-2P C474952
USB-B,J5,USB_B_OST_USB-B1HSxx_Horizontal,C720549,XUNPU USB-B10-BRW,"THT; proveri crtez otiska, original OST C3198024"
SWD,J6,PinHeader_1x03_P2.54mm_Vertical,C49257,BOOMELE 2.54-1*3P,THT
100uH SRR1280-101M,L1,L_Bourns_SRR1260,C2041361,Bourns SRR1280-101M,"isti otisak kao SRR1260; Isat 2,0 A"
2N7002,"Q2,Q5,Q6,Q7",SOT-23,C8545,CJ 2N7002,
TIP122 + hladnjak,Q3,TO-220-3_Vertical,C84073,CJ TIP122,"THT, polozen na hladnjak"
MMBT3904,Q4,SOT-23,C20526,CJ MMBT3904,"umesto BC847, isti raspored B-E-C"
1k,"R3,R6,R15",R_0805_2012Metric,C17513,UNI-ROYAL 0805W8F1001T5E,
15k,R4,R_0805_2012Metric,C17475,UNI-ROYAL 0805W8F1502T5E,
3k24,R5,R_0805_2012Metric,C17609,UNI-ROYAL 0805W8F3241T5E,
1R2 1W,R7,R_2512_6332Metric,C46193,UNI-ROYAL 25121WF120KT4E,"1 W, 1 %"
91k,R8,R_0805_2012Metric,C137484,Yageo RC0805FR-0791KL,ne C17855 (9k1)
10k,"R9,R11,R13,R17,R20",R_0805_2012Metric,C17414,UNI-ROYAL 0805W8F1002T5E,
100k,"R10,R12,R18",R_0805_2012Metric,C149504,UNI-ROYAL 0805W8F1003T5E,
1R 1W,R14,R_2512_6332Metric,C11254,UNI-ROYAL 25121WF100KT4E,"1 W, 1 %"
40k2,R16,R_0805_2012Metric,C17678,UNI-ROYAL 0805W8F4022T5E,
100,R19,R_0805_2012Metric,C17408,UNI-ROYAL 0805W8F1000T5E,
27,"R21,R22",R_0603_1608Metric,C25190,UNI-ROYAL 0603WAF270JT5E,
10k,"R23,R25,R34,R35",R_0603_1608Metric,C25804,UNI-ROYAL 0603WAF1002T5E,
1k,"R24,R26,R27,R36",R_0603_1608Metric,C21190,UNI-ROYAL 0603WAF1001T5E,
3k0,R30,R_0805_2012Metric,C17661,UNI-ROYAL 0805W8F3001T5E,
53k6,R31,R_0805_2012Metric,C322510,FH RS-05K5362FT,
2k,R32,R_0805_2012Metric,C17604,UNI-ROYAL 0805W8F2001T5E,
3k3,R33,R_0603_1608Metric,C22978,UNI-ROYAL 0603WAF3301T5E,
100k,R37,R_0603_1608Metric,C25803,UNI-ROYAL 0603WAF1003T5E,
BOOTSEL,SW1,SW_Push_1P1T_XKB_TS-1187A,C318884,XKB TS-1187A-B-A-B,
RESET,SW2,SW_Push_1P1T_XKB_TS-1187A,C318884,XKB TS-1187A-B-A-B,
LM2587S-ADJ,U1,TO-263-5_TabPin3,C1355343,TI LM2587S-ADJ/NOPB,malo na stanju
R-78E5.0-0.5,U2,Converter_DCDC_RECOM_R-78E-0.5_THT,C5199916,RECOM R-78E5.0-0.5,THT
REF3033,U3,SOT-23,C36658,TI REF3033AIDBZR,
OPA197,U4,SOIC-8_3.9x4.9mm_P1.27mm,C79274,TI OPA197IDR,
MCP6002,U5,SOIC-8_3.9x4.9mm_P1.27mm,C7377,Microchip MCP6002T-I/SN,
MCP6561,"U6,U12",SOT-23-5,C117501,Microchip MCP6561T-E/OT,samo OT varijanta
ADuM3160,U8,SOIC-16W_7.5x10.3mm_P1.27mm,C108501,ADI ADuM3160BRWZ,malo na stanju
RP2040,U9,QFN-56-1EP_7x7mm_P0.4mm_EP3.2x3.2mm,C2040,Raspberry Pi RP2040,
W25Q16JVSS,U10,SOIC-8_5.23x5.23mm_P1.27mm,C131025,Winbond W25Q16JVSSIQ,
AP2112K-3.3,U11,SOT-23-5,C51118,Diodes AP2112K-3.3TRG1,
12MHz,Y1,Crystal_SMD_3225-4Pin_3.2x2.5mm,C9002,YXC X322512MSB4SI,CL 20 pF
